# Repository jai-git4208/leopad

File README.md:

# LEOPAD - The 8-Key Macropad

LEOPAD (Layout Enhancement & Optimization Pad or a cute cat :3 ) is an 8-key programmable designed specifically for developers and programmers. It streamlines your coding workflow with dedicated shortcuts for common programming tasks, Git operations, and system controls.

## Why LEOPAD?

As developers, we constantly switch between coding, debugging, version control, and managing our workspace. LEOPAD puts the most essential shortcuts right at your fingertips with an intuitive 8-key layout that includes an OLED display for visual feedback and RGB lighting for style.

## Features

- **8 Mechanical Keys** - Cherry MX-compatible switches for tactile feedback
- **OLED Display** (128x64) - Real-time mode and key function display
- **RGB Backlighting** - 2x SK6812MINI addressable LEDs
- **4 Layer System**:
  - **Programming Mode** - Core coding shortcuts (Run/Build, Comment, Format, etc.)
  - **Git Mode** - Version control commands
  - **System Mode** - Media and window controls
  - **Custom Mode** - Programmable function keys (F13-F18)
- **KMK Firmware** - Python-based, easy to customize
- **Compact Design** - ~95mm x 80mm footprint

## Schematic

The circuit is built around the Seeed XIAO RP2040 microcontroller with:
- 8 push button switches with pull-down configuration
- 1x SSD1306 OLED display (I2C interface)
- 2x SK6812MINI RGB LEDs in series
- USB-C connectivity through the XIAO

## PCB Design

## Case Design

## Bill of Materials (BOM)

| Component | Quantity | Notes |
|-----------|----------|-------|
| Seeed XIAO RP2040 | 1 | Microcontroller |
| Cherry MX Compatible Switch | 8 | Your choice of switch type |
| Keycaps | 8 | 1U keycaps |
| SSD1306 OLED Display | 1 | 128x64, I2C interface |
| SK6812MINI RGB LED | 2 | Addressable RGB |
| 1N4148 Diode | 8 | Through-hole or SMD |
| Push Button Switch (SW_Push) | 8 | Alternative to MX switches |
| 3D Printed Case | 1 set | Top + Bottom pieces |
| M3 Screws | 4 | Optional, for case assembly |
| M3 Heat-set Inserts | 4 | Optional, for case |
| Rubber Feet | 4 | Anti-slip pads |

## Key Layout

### Layer 0: Programming Mode (Default)
```
┌─────┬─────┬─────┬─────┐
│ F5  │Ctrl+/│Ctrl+D│S+A+F│
│ Run │Cmt  │Dupl │Fmt  │
├─────┼─────┼─────┼─────┤
│Ctrl+`│C+S+F│C+S+G│Layer│
│Term │Srch │Git  │ ->  │
└─────┴─────┴─────┴─────┘
```

- **Key 1**: F5 - Run/Build current project
- **Key 2**: Ctrl+/ - Comment/Uncomment code
- **Key 3**: Ctrl+D - Duplicate line
- **Key 4**: Shift+Alt+F - Format document
- **Key 5**: Ctrl+` - Open terminal
- **Key 6**: Ctrl+Shift+F - Project-wide search
- **Key 7**: Ctrl+Shift+G - Open Git panel
- **Key 8**: Switch to Git Mode

### Layer 1: Git Mode
```
┌─────┬─────┬─────┬─────┐
│ Git │Cmit │Cmd  │Palte│
│Panel│Enter│Prfx │     │
├─────┼─────┼─────┼─────┤
│ Esc │Undo │RGB  │Layer│
│     │     │Togl │ ->  │
└─────┴─────┴─────┴─────┘
```

- Git operations and commands
- RGB lighting control
- Switch to System Mode

### Layer 2: System Mode
```
┌─────┬─────┬─────┬─────┐
│ New │Close│Next │Prev │
│ Win │ Tab │Tab  │Tab  │
├─────┼─────┼─────┼─────┤
│Vol+ │Vol- │Mute │Layer│
│     │     │     │ ->  │
└─────┴─────┴─────┴─────┘
```

- Window and tab management
- Media controls
- Switch to Custom Mode

### Layer 3: Custom Mode
```
┌─────┬─────┬─────┬─────┐
│ F13 │ F14 │ F15 │ F16 │
│     │     │     │     │
├─────┼─────┼─────┼─────┤
│ F17 │ F18 │ RGB │Layer│
│     │     │ Hue │ ->  │
└─────┴─────┴─────┴─────┘
```

- Programmable function keys
- Map to any software-specific shortcuts
- Back to Programming Mode

## Customization

The firmware is built on KMK, making it easy to customize:

- **Change Key Functions** - Edit the `keyboard.keymap` arrays
- **Add Macros** - Create custom macro sequences
- **Modify Layers** - Add or remove layers as needed
- **Update OLED Display** - Customize what info shows
- **RGB Effects** - Configure lighting patterns

Example custom macro:
```python
CUSTOM_MACRO = KC.MACRO(
    Press(KC.LCTRL), 
    Tap(KC.C), 
    Release(KC.LCTRL),
    # Add your sequence here
)
```

## Design Files

- **PCB**: KiCad project files in `PCB/` folder
- **Case**: STEP and STL files in `CAD/` folder  
- **Firmware**: KMK Python code in `firmware/` folder
- **Resources**: Schematics and images in `resources/` folder

## Preferences

- **PCB Color**: Black
- **Case Color**: Dark Gray / Charcoal

## Credits

Designed and built for the Hack Club Hackpad BLUEPRINT program.

**Designer**: JAIMIN PANSAL  
**GitHub**: jai-git4208
**License**: MIT

## With ❤️ by Jaimin

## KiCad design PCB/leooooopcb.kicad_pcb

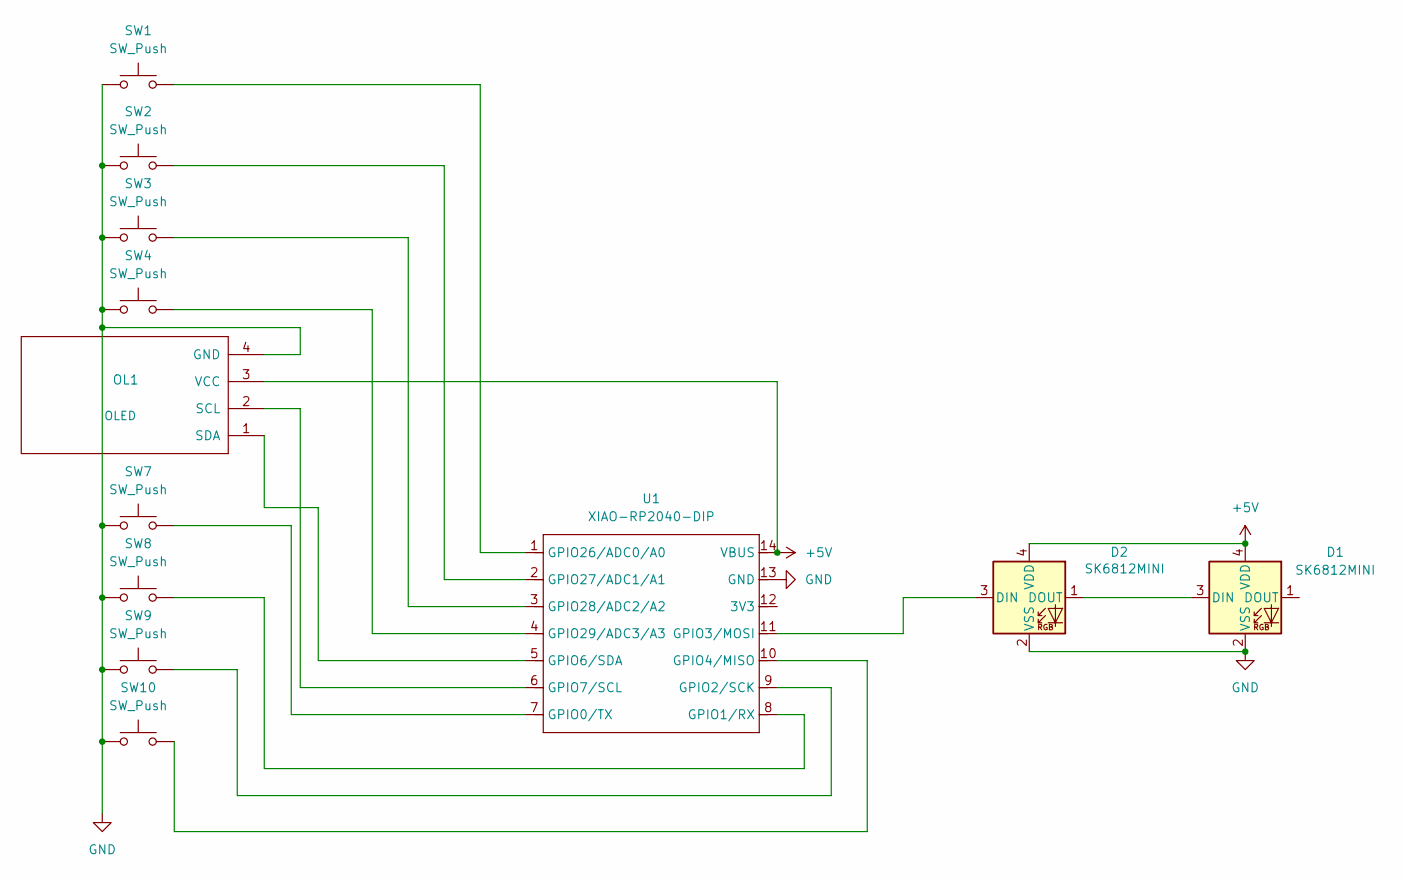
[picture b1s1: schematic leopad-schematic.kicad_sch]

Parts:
D1, D2: SK6812MINI; LED_SK6812MINI_PLCC4_3.5x3.5mm_P1.75mm
OL1: OLED; SSD1306-0.91-OLED-4pin-128x32
SW1, SW2, SW3, SW4, SW7, SW8, SW9, SW10: SW_Push; SW_Cherry_MX_1.00u_PCB
U1: XIAO-RP2040-DIP

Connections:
+5V: D1.4 (VDD), D2.4 (VDD), OL1.3 (VCC), U1.14 (VBUS)
GND: D1.2 (VSS), D2.2 (VSS), OL1.4 (GND), SW1.1, SW2.1, SW3.1, SW4.1, SW7.1, SW8.1, SW9.1, SW10.1, U1.13 (GND)
unnamed: D1.3 (DIN), D2.1 (DOUT)
unnamed: D2.3 (DIN), U1.11 (GPIO3/MOSI)
unnamed: OL1.2 (SCL), U1.6 (GPIO7/SCL)
unnamed: OL1.1 (SDA), U1.5 (GPIO6/SDA)
unnamed: SW7.2, U1.7 (GPIO0/TX)
unnamed: SW8.2, U1.8 (GPIO1/RX)
unnamed: SW9.2, U1.9 (GPIO2/SCK)
unnamed: SW10.2, U1.10 (GPIO4/MISO)
unnamed: SW1.2, U1.1 (GPIO26/ADC0/A0)
unnamed: SW2.2, U1.2 (GPIO27/ADC1/A1)
unnamed: SW3.2, U1.3 (GPIO28/ADC2/A2)
unnamed: SW4.2, U1.4 (GPIO29/ADC3/A3)

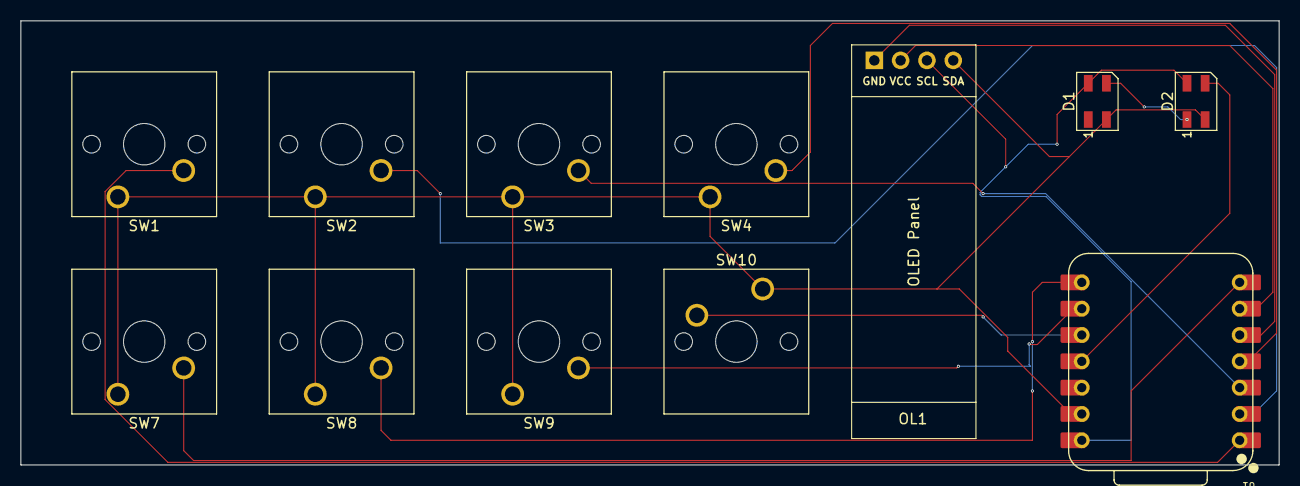
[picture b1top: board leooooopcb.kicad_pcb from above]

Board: 4 copper layers, 121.4 x 42.9 mm, 12 parts (0 on the bottom side), 14 nets.

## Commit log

2025-11-30 add fusion360 case model
2025-11-30 add pcb resources
2025-11-30 add kicad pcd files
2025-11-30 add firmware file
2025-11-30 add README.md
2025-12-05 add 3d printer compatible model
2025-12-11 change diameter
